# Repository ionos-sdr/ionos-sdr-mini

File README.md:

# Ionos SDR mini

Simplified, low-cost sibling of [Ionos SDR](https://github.com/ionos-sdr/ionos-sdr): a carrier PCB that turns a stock Silicon Labs radio board into a usable SDR. An ESP32-S3 DevKitC sits on female headers on the left, a Silicon Labs radio board plugs into the mezzanine socket on the right, and both displays are optional. No custom RF design, no exotic parts — the radio board you already have in a drawer does the RF.

*v1.1, 4 layers. KiCad 10 ray-traced render: DevKitC on headers, SSD1306 OLED with BACK/OK below it, the optional ER-TFTM024-3 TFT on a 2x20 socket in the middle (manufacturer's 3D model), cursor keys and the radio board connectors on the right. The render shows the shrouded Samtec TFC model; the JLC build uses the unshrouded TFM-120-02-L-D-K-TR on the same footprint.*

**Status: v1.1 (4-layer) designed, not built yet.** The built and measured board is rev-B3 2L (tag [`rev-b3-2l`](https://github.com/ionos-sdr/ionos-sdr-mini/tree/rev-b3-2l)) — ≈ 86 hours of measurements plus over-the-air receive tests ([Measurements](#measurements)). The firmware lives in the [main repository](https://github.com/ionos-sdr/ionos-sdr); this repo holds the carrier board, its documentation and its measurements.

## What it is

- **Carrier only.** 168 x 80 mm, 4-layer (JLC04161H-7628: F.Cu parts + GND / In1 solid GND / In2 power + signals, horizontal / B.Cu signals, vertical + GND), four M3 nylon standoffs. No RF layout risk: matching network, SMA and shielding stay on the Silicon Labs radio board. Earlier revisions: rev-B3 2L (built and measured, tag `rev-b3-2l`) and rev-B3 4L (branch `layout/rev-b3`).
- **Any radio board fits.** The mezzanine pair is the standard WSTK radio board interface, so BRD4265B (FG23, 434 MHz, 10 dBm) is only the first panel. The pin-to-signal mapping differs per panel and is selected in firmware.
- **Panel auto-detect.** The radio board's M24C02 board-ID EEPROM sits on the same I2C bus as the OLED, so the firmware can read which panel is plugged in and load the matching pin map at boot.
- **Bootstrap flashing.** SWDIO, SWCLK, SWO and RESET are routed to the ESP32, which bit-bangs SWD. A blank radio board can be programmed with nothing but this board and a USB cable; routine updates then go over the UART command link. For a J-Link or Simplicity Link there is also a 1x6 2.54 mm SWD footprint (CON3) on the right edge.
- **One cable.** Power and data over the DevKit's USB-C. The radio gets its own low-noise LDO from the 5 V rail, not the DevKit's shared 3.3 V.

## Architecture

- **RX**: FG23 I/Q capture and server-side FFT lines over SPI2 (IO_MUX) to the ESP32-S3, then to the host or to the on-board display.
- **Control**: RDY handshake and a UART command link; SWD is bit-banged by the ESP32 so a blank panel can be programmed with nothing but this board.
- **Power**: a single low-noise LDO feeds VMCU_IN; the radio board's own DC-DC handles PAVDD, so one supply pin powers the whole panel.

## Hardware

| Block | Part | Notes |
| --- | --- | --- |
| MCU | ESP32-S3-DevKitC-1 or the AliExpress clone | On 1x22 female headers (JLC-fitted), antenna end overhanging the board edge; see [DevKit: clone or official](#devkit-clone-or-official) |
| Radio | Silicon Labs radio board | 2x 2x20, 1.27 mm mezzanine, 24 mm apart; BRD4265B validated first |
| Display (optional) | EastRising ER-TFTM024-3, 2.4", ILI9341 | 240x320, TE pin wired for tear-free hardware scroll; resistive or capacitive touch |
| Display (optional) | SSD1306 0.96" OLED, I2C | Status line when the large display is not fitted |
| Buttons | 6+1 tactile, C&K PTS647 | UP/DOWN/LEFT/RIGHT plus BACK/OK, a seventh SPARE footprint (key optional); two resistor ladders |
| Debug (optional) | 1x6 2.54 mm SWD footprint, CON3 | Not fitted; pogo clip or solder-in pins, see below |
| Radio supply | LP5907-3.3 or TPS7A2033 | ~6.5 uVrms, fed from the DevKit 5 V rail, ferrite + 10 uF at the connector |

Seven keys cost two pins, not seven: both ladders use the same 10 k pull-up and the same 0 R / 2.2 k / 6.8 k / 22 k set to GND (UP/DOWN/LEFT/RIGHT on GPIO2, BACK/OK/SPARE on GPIO1, the 22 k level of that ladder left free), read on ADC1 with a 1 k + 100 nF filter at the pin. One threshold table serves both: 0.30 / 0.97 / 1.80 / 2.79 V. Only the 0 R keys (UP, BACK) can wake the chip from deep sleep. The freed GPIOs carry the SWD lines.

## Pin mapping (BRD4265B)

The EXP header numbers come from the Silicon Labs radio board documentation; the connector pins are what you actually route. For EXP 3 to 16 the P201 pin number equals the EXP number.

| Signal | ESP32-S3 GPIO | FG23 pin | WSTK net | Connector pin |
| --- | --- | --- | --- | --- |
| SCLK | 12 (SPI2 IO_MUX) | PC05 | WSTK_P12 | P201-15 |
| MOSI | 11 (SPI2 IO_MUX) | PC00 | WSTK_P7 | P201-10 |
| CS | 10 (SPI2 IO_MUX) | PA07 | WSTK_P10 | P201-13 |
| RDY | 14 | PD02 | WSTK_P6 | P201-9 |
| CMD | 13 (UART TX) | PA06 | WSTK_P8 | P201-11 |
| SWDIO | 38 | PA02 | WSTK_P18 | P201-21 |
| SWCLK | 39 | PA01 | WSTK_P20 | P201-23 |
| SWO | 47 | PA03 | WSTK_P16 | P201-19 |
| RESETn | 40 | RESETn | WSTK_F4 | P200-17 |
| BOARD_ID_SDA / SCL | 41 / 42 (I2C0) | - | BOARD_ID | P200-40 / P200-39 |
| VMCU_IN | - | - | VMCU_IN | P201-2 |
| 3V3 | - | - | 3V3 | P200-1 |
| GND | - | - | GND | P200-2, 38; P201-1, 39 |

The FG23 link runs on SPI2 through the IO_MUX pins so the slave interface keeps its headroom for higher clocks; the optional TFT is on SPI3. `VRF` is unused on BRD4265B and the on-board DC-DC feeds PAVDD, so a single supply pin powers the whole panel; P201-40 (VRF_IN) only runs to test point TP8, and P200-37 (5 V) has a not-fitted 0 R (R33) from the DevKit 5 V for panels that need it.

## Display and touch

The ER-TFTM024-3 sits on SPI3 (SCK 4, MOSI 5, MISO 6, CS 7, D/C 15, RST 16, BL 17, TE 18). Its resistive touch controller (XPT2046) and the module's optional SD/font/flash chips share a second header bus (pins 32/33/34), which is tied to the TFT bus on the carrier; the touch transactions run at their own ~2 MHz clock. 10 k pull-ups hold the module's SD/FONT/FLASH chip selects (header 35/36/37) inactive so nothing else drives MISO.

| Pin | Resistive (XPT2046) | Capacitive (I2C CTP) |
| --- | --- | --- |
| TCH_A, GPIO8, header 30 | SPI CS | I2C SCL |
| TCH_B, GPIO21, header 31 | PENIRQ | I2C SDA |
| TCH_INT, GPIO9, header 39 | unused | CTP INT |

Both 4.7 k pull-ups (TCH_A, TCH_B) are fitted in every build, so one BOM serves both panel types; firmware picks the mode. **Before the first power-up**, measure the panel's MISO/TE high level with VDD = 5 V: if it follows 5 V, run the panel from 3V3 or add level shifting.

## DevKit: clone or official

The two boards do not share the same header spacing. On the Espressif ESP32-S3-DevKitC-1 the two pin rows are 22.86 mm apart. The AliExpress clone is wider: its PCB is 28.3 mm, and its rows are 25.4 mm apart.

Since v1.1 the footprint has both right-hand rows:
- J1 (left) is shared.
- J3 has two rows of holes, 2.54 mm apart, joined by copper.
- The silkscreen shows both outlines (the clone's dashed) and marks the two spacings, "DevKitC-1 22.86" and "clone 25.40", under the module.

JLC fits the female headers:

| Header | Row | Fitted |
| --- | --- | --- |
| J10 | J1 (shared) | always |
| J11 | clone J3 | default |
| J12 | DevKitC-1 J3 | not fitted (DNP); fit it instead of J11 for an Espressif board |

The RGB LED is on GPIO48 on the clone and on DevKitC-1 v1.0, and on GPIO38 on DevKitC-1 v1.1. The SWD lines avoid GPIO48: since v1.1 SWO is on **GPIO47**, SWDIO stays on GPIO38. With a DevKitC-1 v1.1 the LED sits on SWDIO, flickers during SWD and loads the line, so remove the LED or its series resistor, or use the clone or a v1.0 board.

## Changes in v1.1

- DevKit footprint with two J3 rows (clone 25.4 mm and DevKitC-1 22.86 mm), J10-J12 female headers in the JLC BOM (Hong Cheng HC-PM254-8.5H-1x22PZ, THT).
- SWO moved from GPIO48 to GPIO47 (GPIO48 drives the clone's RGB LED).
- OLED: four 2.5 mm plated holes for the module's mounting lugs, and the outline per the module drawing (27.3 x 27.3 mm).
- TFT socket is SMD (HCTL PM254-2-20-S-8.5, 8.5 mm), assembled by JLC.
- Layer roles: In1 is solid GND, as the reference for the top layer. In2 carries the power and most signals, routed horizontally (89 % of its length); B.Cu takes the vertical runs (79 %). The top layer holds only the parts' escapes (153 mm). The board was fully re-routed and GND-stitched.

## SWD debug header

CON3 is a 1x6 2.54 mm row of plated holes on the right edge, outside the radio board's outline, so it stays reachable with the radio board plugged in. Pin order follows the Tag-Connect TC2030-CTX:

| Pin | 1 | 2 | 3 | 4 | 5 | 6 |
| --- | --- | --- | --- | --- | --- | --- |
| Signal | VTref (VMCU) | SWDIO | nRESET | SWCLK | GND | SWO |

The pins connect on the radio side of the solder-jumper cut points. With a debugger attached, either keep the ESP32's SWD pins as inputs in firmware or cut JP2 and JP6-JP8 to detach the ESP32 completely. VTref only senses the radio board's VMCU; the debugger must not power the board through it.

## Measurements

All measurements so far are on **rev-B3 2L** + BRD4265B, the board that was built (tag [`rev-b3-2l`](https://github.com/ionos-sdr/ionos-sdr-mini/tree/rev-b3-2l)); v1.1 has not been built yet.

**Time on test so far: ≈ 86 hours** (rev-B3 2L + BRD4265B, 2–9 Nov 2026): ≈ 54 h RF with a calibrated signal generator, ≈ 32 h USB-only soaks.
Full report: [`docs/ionos-mini-measurements-2026-11.md`](docs/ionos-mini-measurements-2026-11.md) ([magyarul](docs/hu/ionos-mini-meresi-jelentes-2026-11.md)) · raw data and scripts: [`measurements/ionos-mini-2026-11/`](measurements/ionos-mini-2026-11/).

| BRD4265B (434 MHz match), measured at 145 MHz | |
|---|---|
| I/Q over USB (TinyUSB CDC on USB‑OTG) | 200 ksps int16 (813 kB/s); 40 h: 86 M blocks, 0 device drops, 0.65 ppm host loss |
| Gain / clipping | dBFS = P_in + 53.68 dB (σ 0.10 dB over 40 h), clip ≈ −52 dBm |
| NF / MDS | ≈ 8.6 dB / ≈ −128 dBm (10 dB SNR, 500 Hz) |
| 200 ksps bandwidth / image rejection | 88 kHz at −3 dB (PHY channel filter) / ≥ 42 dB |
| Frequency | crystal +4.2 ppm raw (firmware correction currently over-corrects to −11 ppm), 1.9 ppm p‑p diurnal |
| Tuning range with the 145 MHz PHY | 128.34 – 198.07 MHz; CW NF 7.9 – 11.9 dB across it |
| 2‑FSK 5 kbps, BER 10⁻² | median −110 dBm (simple discriminator reference) |
| SoapySDR | SoapyIonos driver works on Windows (GQRX, SoapySDRUtil, Python); 3.25 M blocks in the sweeps, 4 lost |
| Known artefact | ±6.25 kHz sidebands (−74 dBc at 5 kHz, −43 dBc at 37 kHz tone offset) from the I/Q path — open |

### Receive tests, 22 Nov 2026 — APRS, AIS, ground loop

Over the air at home (Budapest, ~1 km from the Danube), mag‑mount 2 m whip on a radiator. Details: [`measurements/ionos-mini-2026-11-22-rx/`](measurements/ionos-mini-2026-11-22-rx/RESULT.md).

| | |
|---|---|
| APRS 144.800, on‑device AFSK demod | channel FIR before the discriminator: 20 of 20 bursts on a 20‑min capture (old firmware 0); ~25 packets/h gated live |
| AIS 161.975 (channel A), on‑device GMSK demod | battery supply: 56 of 63 bursts (89 %); live 70 min: 788 messages, 82 stations (64 river AtoN, 14 vessels); NMEA on TCP 10110 |
| AIS per‑packet level / SNR / offset | −46 … −36 dBFS, SNR 9–25 dB (median 15), ±600 Hz |
| **Ground loop** (mains‑charged laptop USB + antenna on a radiator, no PE in the house) | 12–17 dB gain dips, 2–4 ms, every 20 ms: AIS 13 of 398 bursts, APRS dead after dark. **Use a battery or isolate the USB.** |

<p align="center"><i>On‑device TFT waterfall (PC emulator of the firmware): old vs new — per‑bin peak of the 3 FFTs per row, 24 dB range, DC patch ±1 bin.</i></p>

### AIS: I/Q path vs FG23 on-chip, 23 Nov 2026 — VSG60 and live

Same firmware, two receive modes: the ESP32 demodulates the FG23's I/Q stream, or the FG23 decodes AIS itself (own PHY, LEGACY demod, HDLC/CRC on-chip). Details: [`measurements/ionos-mini-2026-11-23-ais-onchip/`](measurements/ionos-mini-2026-11-23-ais-onchip/RESULT.md).

| | I/Q path | FG23 on-chip |
|---|---|---|
| 50 % PER (VSG, 10 bursts/s, 26 cycles overnight) | −106.19 dBm (sd 0.17) | −105.45 dBm (sd 0.10) |
| frequency offset at −103 dBm, PER ≤ 7 % | about ±1 kHz | about ±3 kHz |
| CW on channel B (+50 kHz), +30 dBc | channel A blocked (alias) | no loss up to +50 dBc |
| every slot busy (37.5 bursts/s, −96 dBm) | 0 % | 0 % |
| live, 15 h alternating (Danube) | 1.67 msgs/min (721) | 2.08 msgs/min (902) |
| channels | A | A or B |

**Full AIS report (PDF, rev. 2, 26 Nov 2026)** - instrument (VSG60A) and field tests, test hours, charts, and **dual-channel I/Q: channels A and B at the same time from one FG23, measured overnight** (no sensitivity cost, +/-4 kHz offset tolerance with AFC): [English](docs/reports/ionos-mini_AIS_report_EN_2026-11-26.pdf)  [Magyar](docs/reports/ionos-mini_AIS_jelentes_HU_2026-11-26.pdf). Dual-channel data: [`measurements/ionos-mini-2026-11-25-ais-dual/`](measurements/ionos-mini-2026-11-25-ais-dual/RESULT.md). First edition (25 Nov): [EN](docs/reports/ionos-mini_AIS_report_EN_2026-11-25.pdf) [HU](docs/reports/ionos-mini_AIS_jelentes_HU_2026-11-25.pdf). Live AISBENCH log and the chart/report scripts are in [`measurements/ionos-mini-2026-11-23-ais-onchip/`](measurements/ionos-mini-2026-11-23-ais-onchip/).

## Manufacturing files

Gerbers, drill, JLCPCB BOM and CPL are attached to the GitHub release [`rev-b3-4l-20261022`](https://github.com/ionos-sdr/ionos-sdr-mini/releases/tag/rev-b3-4l-20261022), not committed. To rebuild them from the KiCad project (DRC and schematic parity must be clean, or nothing is written):

```
"C:\Program Files\KiCad\10.0\bin\python.exe" fab/jlc_pack.py
```

JLC assembles the top-side SMD parts, the two radio board connectors, the TFT socket and the DevKit headers (J10 + J11 for the clone by default); the DevKit, the displays and the debug header are fitted by hand. The manufacturing files for v1.1 have not been released yet; the release above is rev-B3 4L, and the built 2L board's files are in [`rev-b3-2l-jlc-20261022`](https://github.com/ionos-sdr/ionos-sdr-mini/releases/tag/rev-b3-2l-jlc-20261022). LCSC part numbers are in `fab/jlc_lcsc.csv`.

## Repository

```
hardware/          KiCad project, fab outputs, BOM           CERN-OHL-P-2.0
docs/              pin mapping, assembly notes, renders      CC-BY-4.0
measurements/      raw data, scripts, results                CC-BY-4.0
firmware/          ESP32-S3 + FG23 source snapshot           MIT
```

Firmware is developed in the [main repository](https://github.com/ionos-sdr/ionos-sdr) (`firmware-fg23/`, `firmware-esp32/`); [`firmware/`](firmware/) here is the snapshot that runs on the measured units, with both AIS receive modes (I/Q and FG23 on-chip). See [`firmware/README.md`](firmware/README.md).

## Credits, licensing, trademarks

Hardware under CERN-OHL-P-2.0, documentation under CC-BY-4.0. Not affiliated with IONOS SE or Silicon Laboratories; EFR32, Simplicity Studio and the WSTK radio board interface are Silicon Labs property, used here for interoperability only.

Designed by Zoltán Dóczi and Zoltán Papp at [Z2 Labs](https://www.z2labs.io/), Budapest. Design and manufacturing support by [Protowoerk](https://www.protowoerk.com).

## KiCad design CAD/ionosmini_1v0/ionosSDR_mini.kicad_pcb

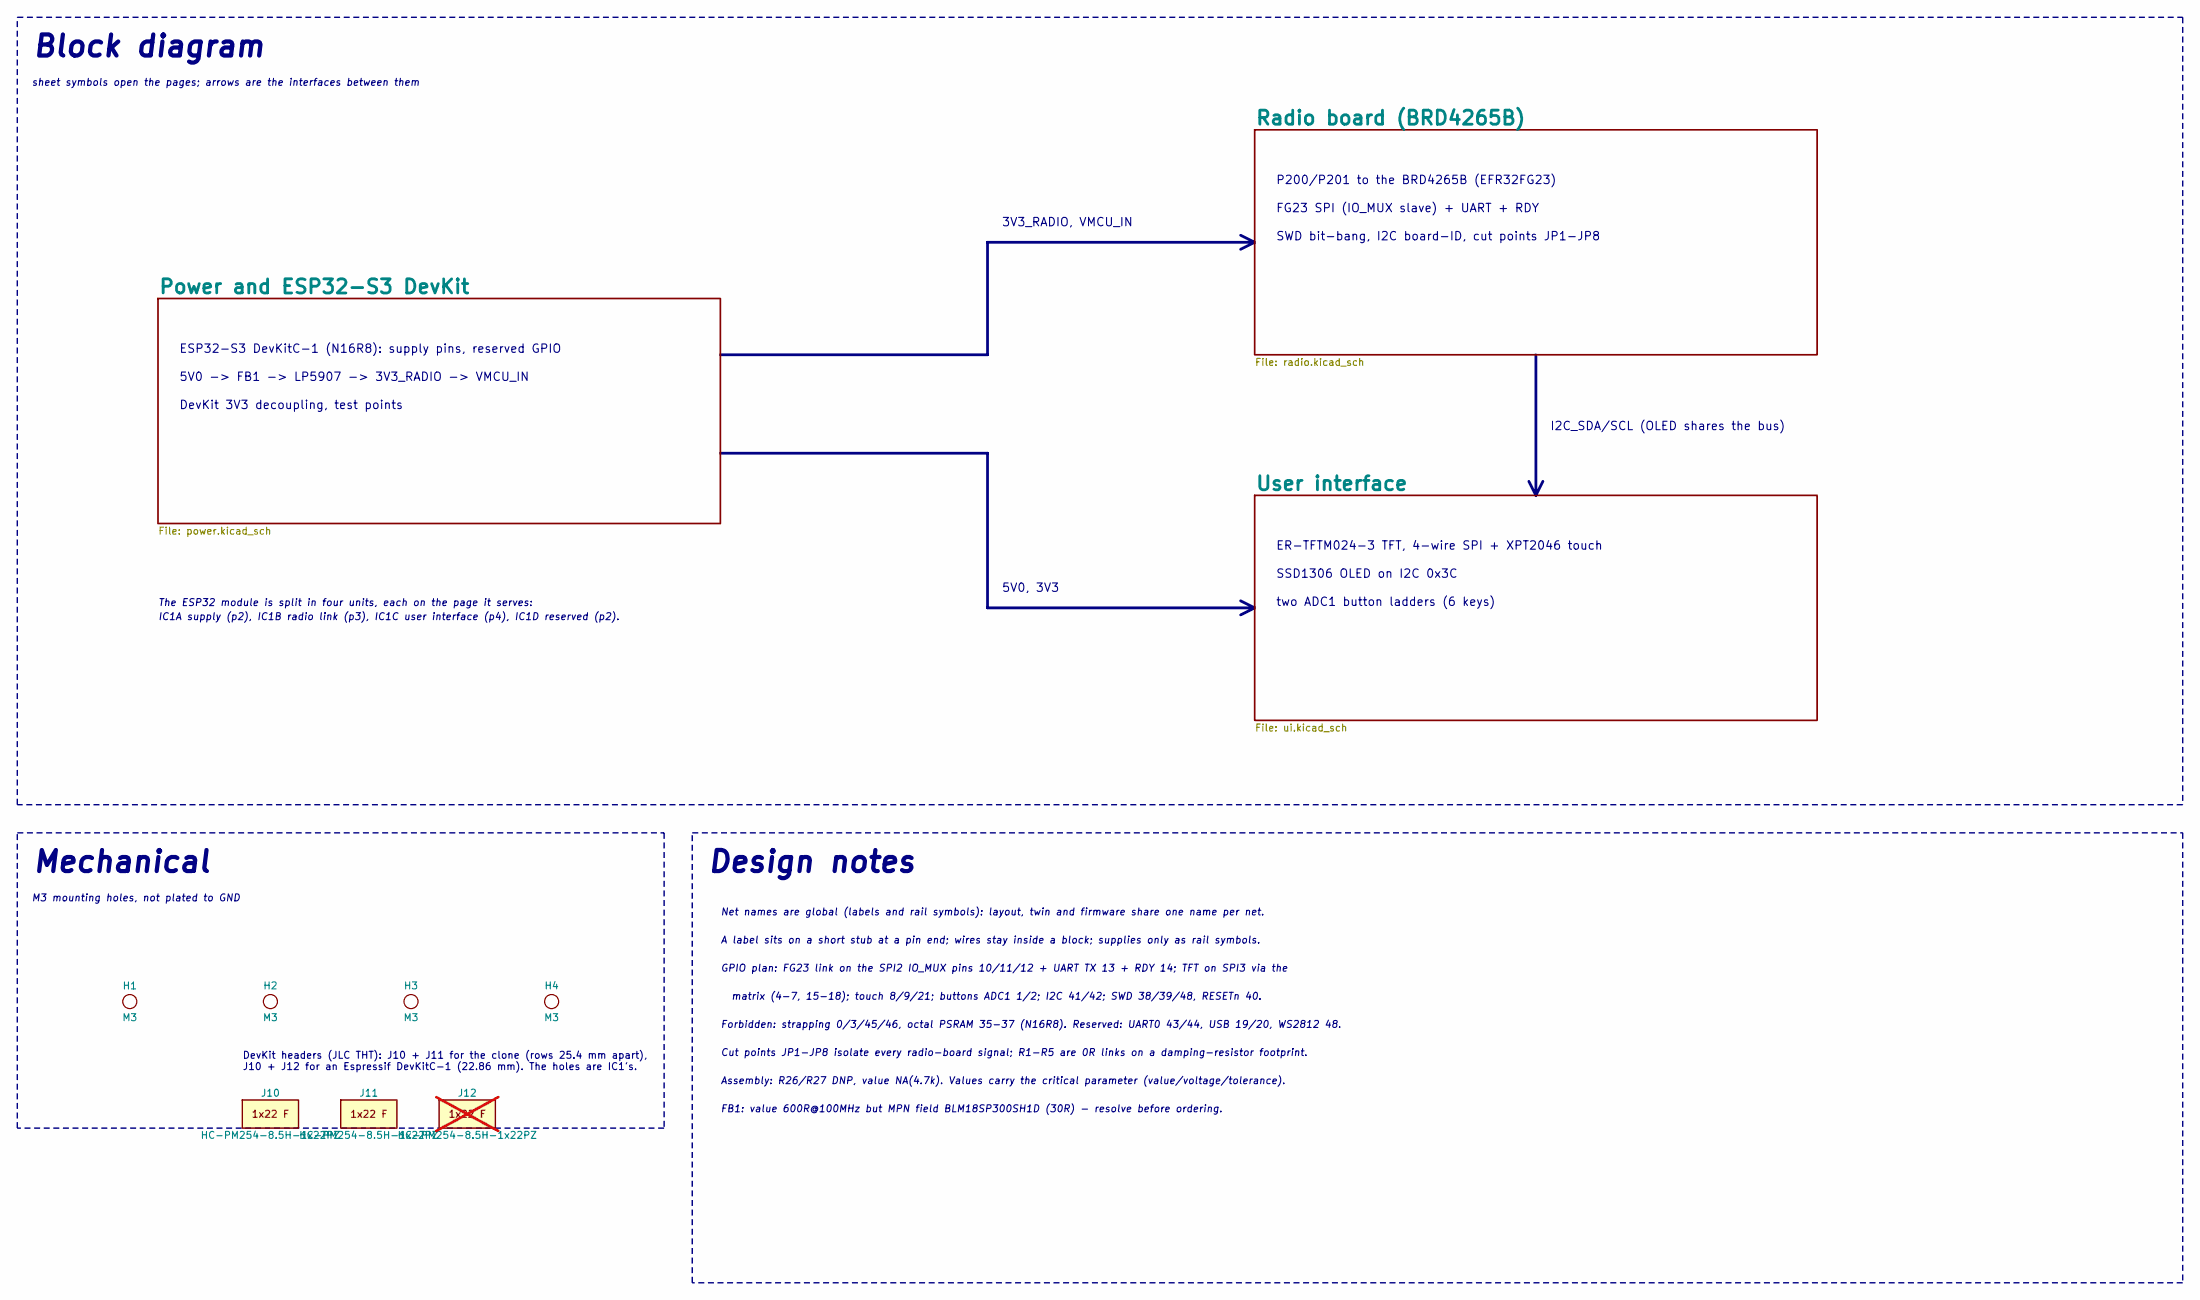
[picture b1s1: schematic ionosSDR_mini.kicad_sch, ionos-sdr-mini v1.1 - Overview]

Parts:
H1, H2, H3, H4: M3; PB_HOLE
J10, J11: HC-PM254-8.5H-1x22PZ; DevKit_Socket_1x22_THT
J12: HC-PM254-8.5H-1x22PZ; DevKit_Socket_1x22_THT; not fitted

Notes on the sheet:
Block diagram
sheet symbols open the pages; arrows are the interfaces between them
ESP32-S3 DevKitC-1 (N16R8): supply pins, reserved GPIO
5V0 -> FB1 -> LP5907 -> 3V3_RADIO -> VMCU_IN
DevKit 3V3 decoupling, test points
P200/P201 to the BRD4265B (EFR32FG23)
FG23 SPI (IO_MUX slave) + UART + RDY
SWD bit-bang, I2C board-ID, cut points JP1-JP8
ER-TFTM024-3 TFT, 4-wire SPI + XPT2046 touch
SSD1306 OLED on I2C 0x3C
two ADC1 button ladders (6 keys)
3V3_RADIO, VMCU_IN
5V0, 3V3
I2C_SDA/SCL (OLED shares the bus)
The ESP32 module is split in four units, each on the page it serves:
IC1A supply (p2), IC1B radio link (p3), IC1C user interface (p4), IC1D reserved (p2).
Mechanical
M3 mounting holes, not plated to GND
Design notes
Net names are global (labels and rail symbols): layout, twin and firmware share one name per net.
A label sits on a short stub at a pin end; wires stay inside a block; supplies only as rail symbols.
GPIO plan: FG23 link on the SPI2 IO_MUX pins 10/11/12 + UART TX 13 + RDY 14; TFT on SPI3 via the
matrix (4-7, 15-18); touch 8/9/21; buttons ADC1 1/2; I2C 41/42; SWD 38/39/48, RESETn 40.
Forbidden: strapping 0/3/45/46, octal PSRAM 35-37 (N16R8). Reserved: UART0 43/44, USB 19/20, WS2812 48.
Cut points JP1-JP8 isolate every radio-board signal; R1-R5 are 0R links on a damping-resistor footprint.
Assembly: R26/R27 DNP, value NA(4.7k). Values carry the critical parameter (value/voltage/tolerance).
FB1: value 600R@100MHz but MPN field BLM18SP300SH1D (30R) - resolve before ordering.
DevKit headers (JLC THT): J10 + J11 for the clone (rows 25.4 mm apart), J10 + J12 for an Espressif DevKitC-1 (22.86 mm). The holes are IC1's.

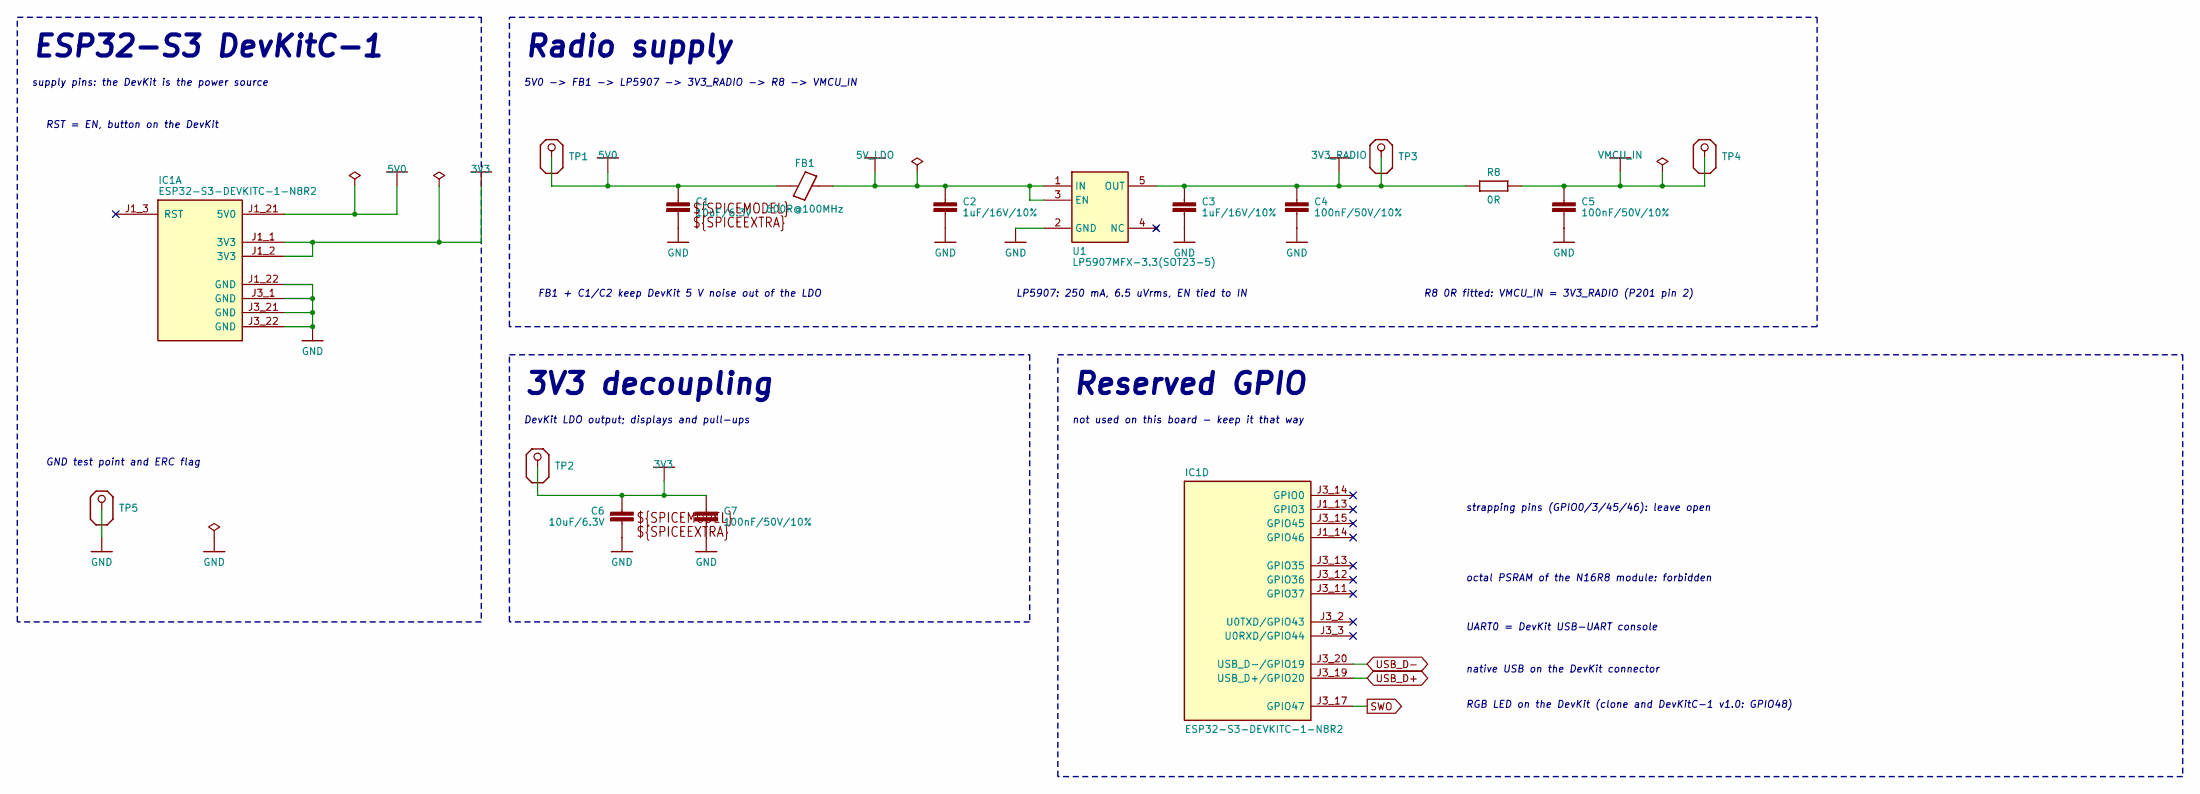
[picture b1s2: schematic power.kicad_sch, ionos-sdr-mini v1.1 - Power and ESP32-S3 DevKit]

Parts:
C1, C6: 10uF/6.3V; CAPC1005X60_0402
C2, C3: 1uF/16V/10%; CAPC1005X60_0402; MPN CL05A105KO5NNNC
C4, C5, C7: 100nF/50V/10%; CAPC1005X60_0402; MPN GRM155R71H104KE14D
FB1: 600R@100MHz; L5_0603; MPN BLM18SP300SH1D
IC1: ESP32-S3-DEVKITC-1-N8R2; XCVR_ESP32-S3-DEVKITC-1-N8R2; MPN ESP32-S3-DEVKITC-1-N8R2
R8: 0R; RESC1005X40_0402; MPN CRCW04020000Z0EDC
TP1: 5V0; TESTPOINT_40MIL_SMD
TP2: 3V3; TESTPOINT_40MIL_SMD
TP3: 3V3_RADIO; TESTPOINT_40MIL_SMD
TP4: VMCU_IN; TESTPOINT_40MIL_SMD
TP5: GND; TESTPOINT_40MIL_SMD
U1: LP5907MFX-3.3(SOT23-5); SOT-23-5; MPN LP5907MFX-3.3/NOPB

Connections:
3V3: C6.1, C7.1, IC1.J1_1 (3V3), IC1.J1_2 (3V3), TP2.PP; also elsewhere on the board
3V3_RADIO: C3.1, C4.1, R8.1, TP3.PP, U1.5 (OUT); also elsewhere on the board
5V0: C1.1, FB1.1, IC1.J1_21 (5V0), TP1.PP; also elsewhere on the board
5V_LDO: C2.1, FB1.2, U1.1 (IN), U1.3 (EN)
GND: C1.2, C2.2, C3.2, C4.2, C5.2, C6.2, C7.2, IC1.J1_22 (GND), IC1.J3_1 (GND), IC1.J3_21 (GND), IC1.J3_22 (GND), TP5.PP, U1.2 (GND); also elsewhere on the board
SWO: IC1.J3_17 (GPIO47); also elsewhere on the board
USB_D+: IC1.J3_19 (USB_D+/GPIO20)
USB_D-: IC1.J3_20 (USB_D-/GPIO19)
VMCU_IN: C5.1, R8.2, TP4.PP; also elsewhere on the board

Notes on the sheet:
ESP32-S3 DevKitC-1
supply pins: the DevKit is the power source
GND test point and ERC flag
RST = EN, button on the DevKit
Radio supply
5V0 -> FB1 -> LP5907 -> 3V3_RADIO -> R8 -> VMCU_IN
FB1 + C1/C2 keep DevKit 5 V noise out of the LDO
LP5907: 250 mA, 6.5 uVrms, EN tied to IN
R8 0R fitted: VMCU_IN = 3V3_RADIO (P201 pin 2)
3V3 decoupling
DevKit LDO output; displays and pull-ups
Reserved GPIO
not used on this board - keep it that way
strapping pins (GPIO0/3/45/46): leave open
octal PSRAM of the N16R8 module: forbidden
UART0 = DevKit USB-UART console
native USB on the DevKit connector
RGB LED on the DevKit (clone and DevKitC-1 v1.0: GPIO48)

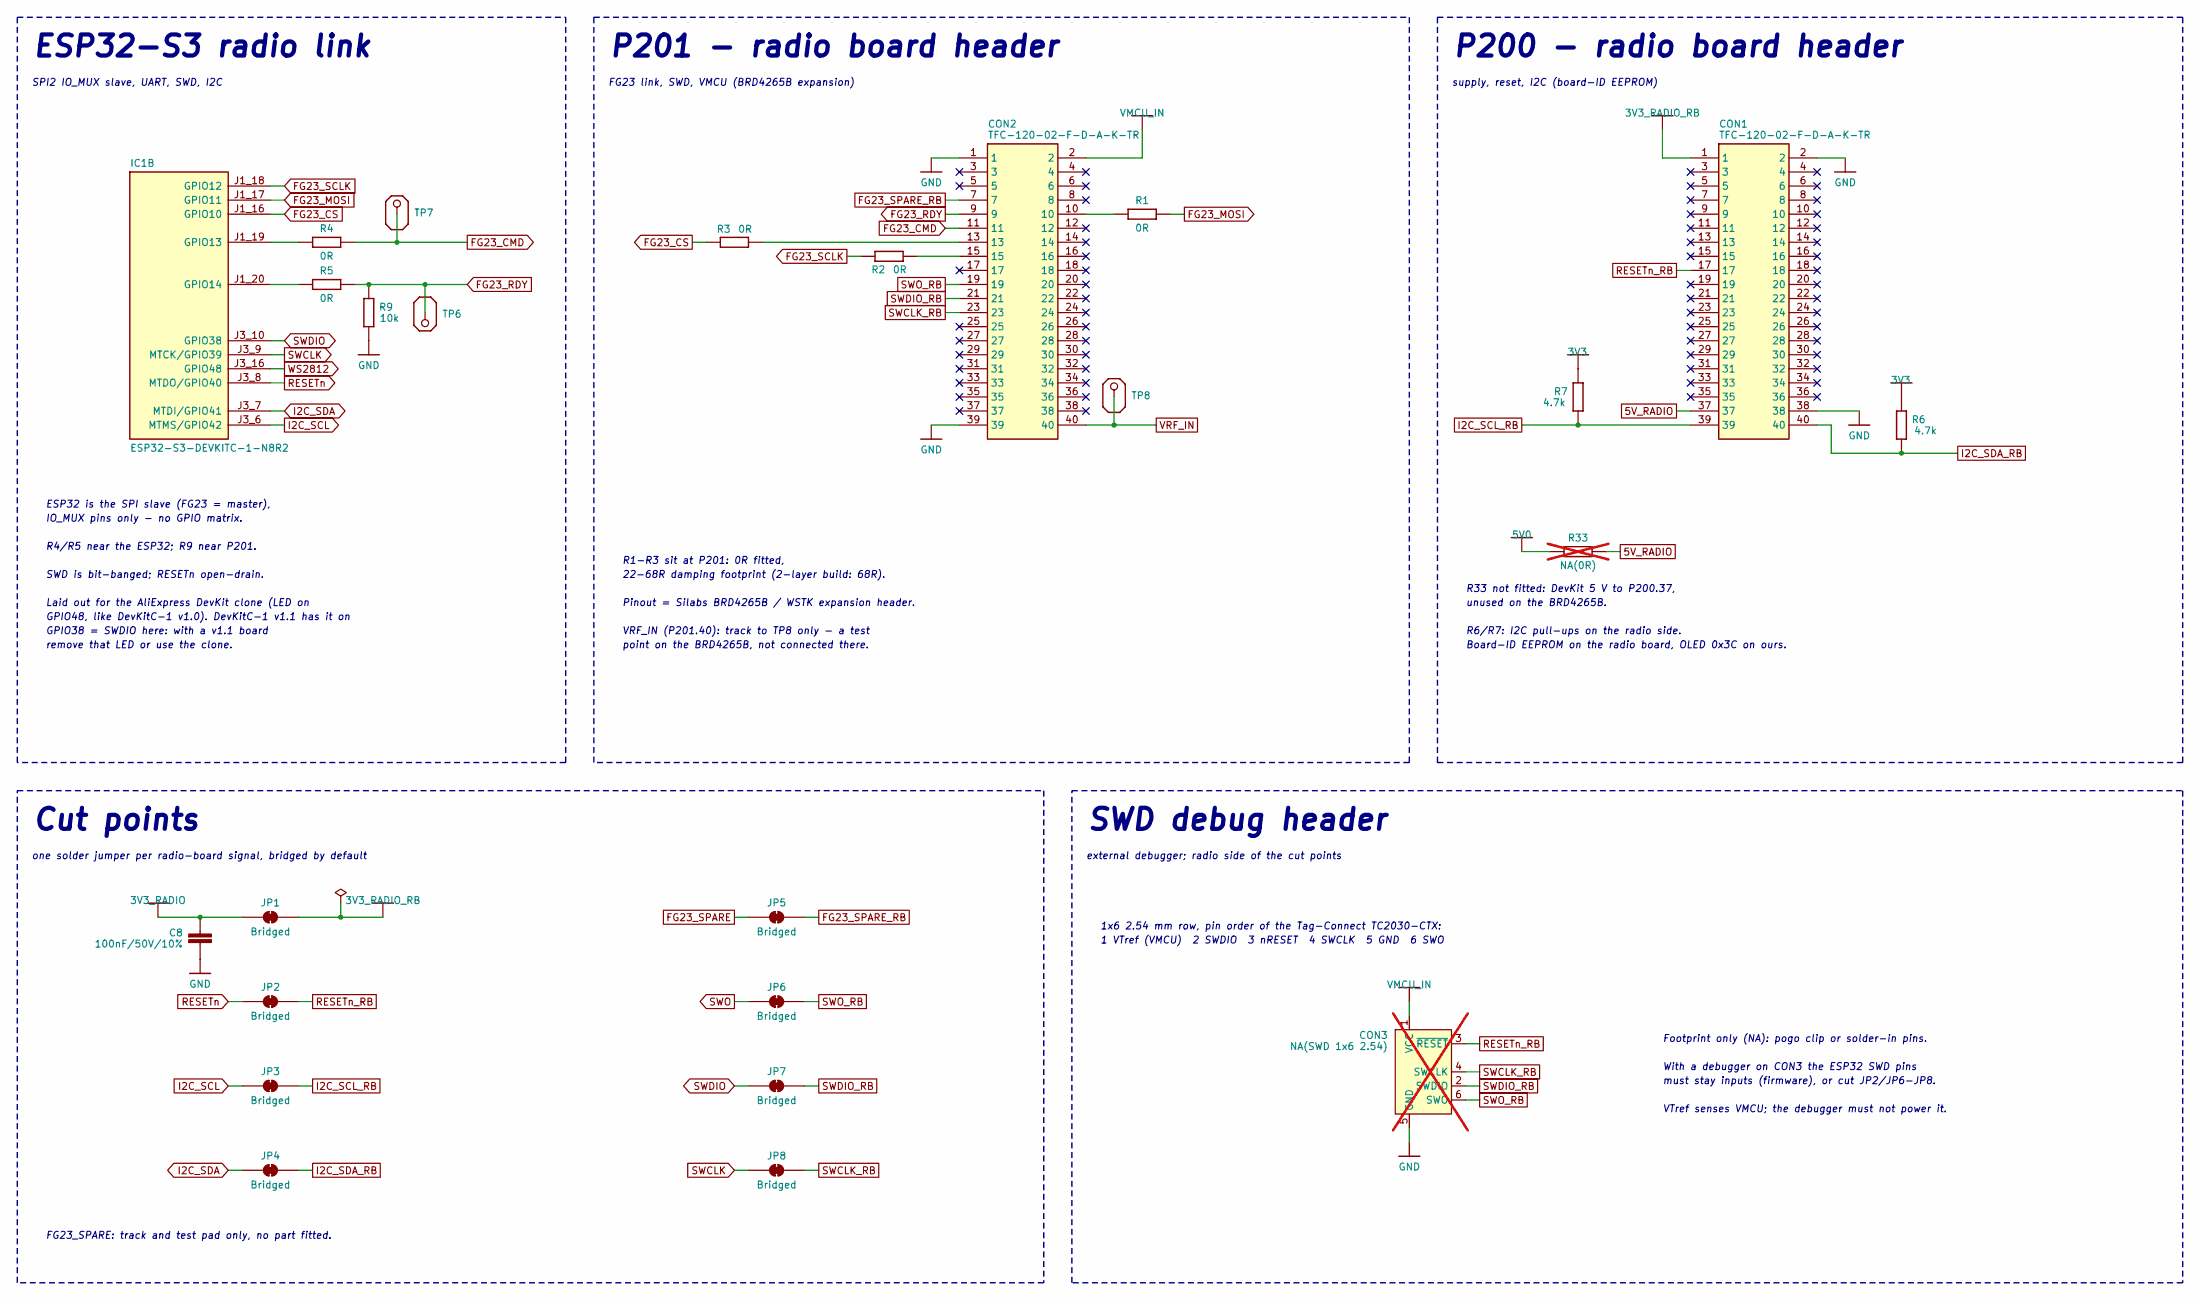
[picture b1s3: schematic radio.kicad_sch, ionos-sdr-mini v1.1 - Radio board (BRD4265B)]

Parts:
C8: 100nF/50V/10%; CAPC1005X60_0402; MPN GRM155R71H104KE14D
CON1, CON2: TFC-120-02-F-D-A-K-TR; TFC-120-02-XX-D-A-K-TR; MPN TFC-120-02-F-D-A-K-TR
CON3: NA(SWD 1x6 2.54); PinHeader_1x06_P2.54mm_Vertical; not fitted
IC1: ESP32-S3-DEVKITC-1-N8R2; XCVR_ESP32-S3-DEVKITC-1-N8R2; MPN ESP32-S3-DEVKITC-1-N8R2
JP1, JP2, JP3, JP4, JP5, JP6, JP7, JP8: Bridged; SolderJumper-2_P1.3mm_Bridged_RoundedPad1.0x1.5mm
R1, R2, R3, R4, R5: 0R; RESC1005X40_0402; MPN CRCW04020000Z0EDC
R6, R7: 4.7k; RESC1005X40_0402; MPN CR0402AJW-472GAS
R9: 10k; RESC1005X40_0402; MPN CRCW040210K0FKED
R33: NA(0R); RESC1005X40_0402; MPN CRCW04020000Z0EDC; not fitted
TP6: FG23_RDY; TESTPOINT_40MIL_SMD
TP7: FG23_CMD; TESTPOINT_40MIL_SMD
TP8: VRF_IN; TESTPOINT_40MIL_SMD

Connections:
3V3: R6.2, R7.2; also elsewhere on the board
3V3_RADIO: C8.1, JP1.1 (A); also elsewhere on the board
3V3_RADIO_RB: CON1.1, JP1.2 (B)
5V0: R33.1; also elsewhere on the board
5V_RADIO: CON1.37, R33.2
FG23_CMD: CON2.11, R4.1, TP7.PP
FG23_CS: IC1.J1_16 (GPIO10), R3.1
FG23_MOSI: IC1.J1_17 (GPIO11), R1.2
FG23_RDY: CON2.9, R5.1, R9.1, TP6.PP
FG23_SCLK: IC1.J1_18 (GPIO12), R2.1
FG23_SPARE: JP5.1 (A)
FG23_SPARE_RB: CON2.7, JP5.2 (B)
GND: C8.2, CON1.2, CON1.38, CON2.1, CON2.39, CON3.5 (GND), R9.2; also elsewhere on the board
I2C_SCL: IC1.J3_6 (MTMS/GPIO42), JP3.1 (A); also elsewhere on the board
I2C_SCL_RB: CON1.39, JP3.2 (B), R7.1
I2C_SDA: IC1.J3_7 (MTDI/GPIO41), JP4.1 (A); also elsewhere on the board
I2C_SDA_RB: CON1.40, JP4.2 (B), R6.1
unnamed: CON2.10, R1.1
unnamed: CON2.13, R3.2
unnamed: CON2.15, R2.2
unnamed: IC1.J1_19 (GPIO13), R4.2
unnamed: IC1.J1_20 (GPIO14), R5.2
RESETn: IC1.J3_8 (MTDO/GPIO40), JP2.1 (A)
RESETn_RB: CON1.17, CON3.3 (~RESET), JP2.2 (B)
SWCLK: IC1.J3_9 (MTCK/GPIO39), JP8.1 (A)
SWCLK_RB: CON2.23, CON3.4 (SWCLK), JP8.2 (B)
SWDIO: IC1.J3_10 (GPIO38), JP7.1 (A)
SWDIO_RB: CON2.21, CON3.2 (SWDIO), JP7.2 (B)
SWO: JP6.1 (A); also elsewhere on the board
SWO_RB: CON2.19, CON3.6 (SWO), JP6.2 (B)
VMCU_IN: CON2.2, CON3.1 (VCC); also elsewhere on the board
VRF_IN: CON2.40, TP8.PP
WS2812: IC1.J3_16 (GPIO48)

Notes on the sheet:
ESP32-S3 radio link
SPI2 IO_MUX slave, UART, SWD, I2C
ESP32 is the SPI slave (FG23 = master),
IO_MUX pins only - no GPIO matrix.
R4/R5 near the ESP32; R9 near P201.
SWD is bit-banged; RESETn open-drain.
Laid out for the AliExpress DevKit clone (LED on
GPIO48, like DevKitC-1 v1.0). DevKitC-1 v1.1 has it on
GPIO38 = SWDIO here: with a v1.1 board
remove that LED or use the clone.
P201 - radio board header
FG23 link, SWD, VMCU (BRD4265B expansion)
VRF_IN (P201.40): track to TP8 only - a test
point on the BRD4265B, not connected there.
R1-R3 sit at P201: 0R fitted,
22-68R damping footprint (2-layer build: 68R).
Pinout = Silabs BRD4265B / WSTK expansion header.
P200 - radio board header
supply, reset, I2C (board-ID EEPROM)
R33 not fitted: DevKit 5 V to P200.37,
unused on the BRD4265B.
R6/R7: I2C pull-ups on the radio side.
Board-ID EEPROM on the radio board, OLED 0x3C on ours.
Cut points
one solder jumper per radio-board signal, bridged by default
FG23_SPARE: track and test pad only, no part fitted.
SWD debug header
external debugger; radio side of the cut points
1x6 2.54 mm row, pin order of the Tag-Connect TC2030-CTX:
1 VTref (VMCU) 2 SWDIO 3 nRESET 4 SWCLK 5 GND 6 SWO
Footprint only (NA): pogo clip or solder-in pins.
With a debugger on CON3 the ESP32 SWD pins
must stay inputs (firmware), or cut JP2/JP6-JP8.
VTref senses VMCU; the debugger must not power it.

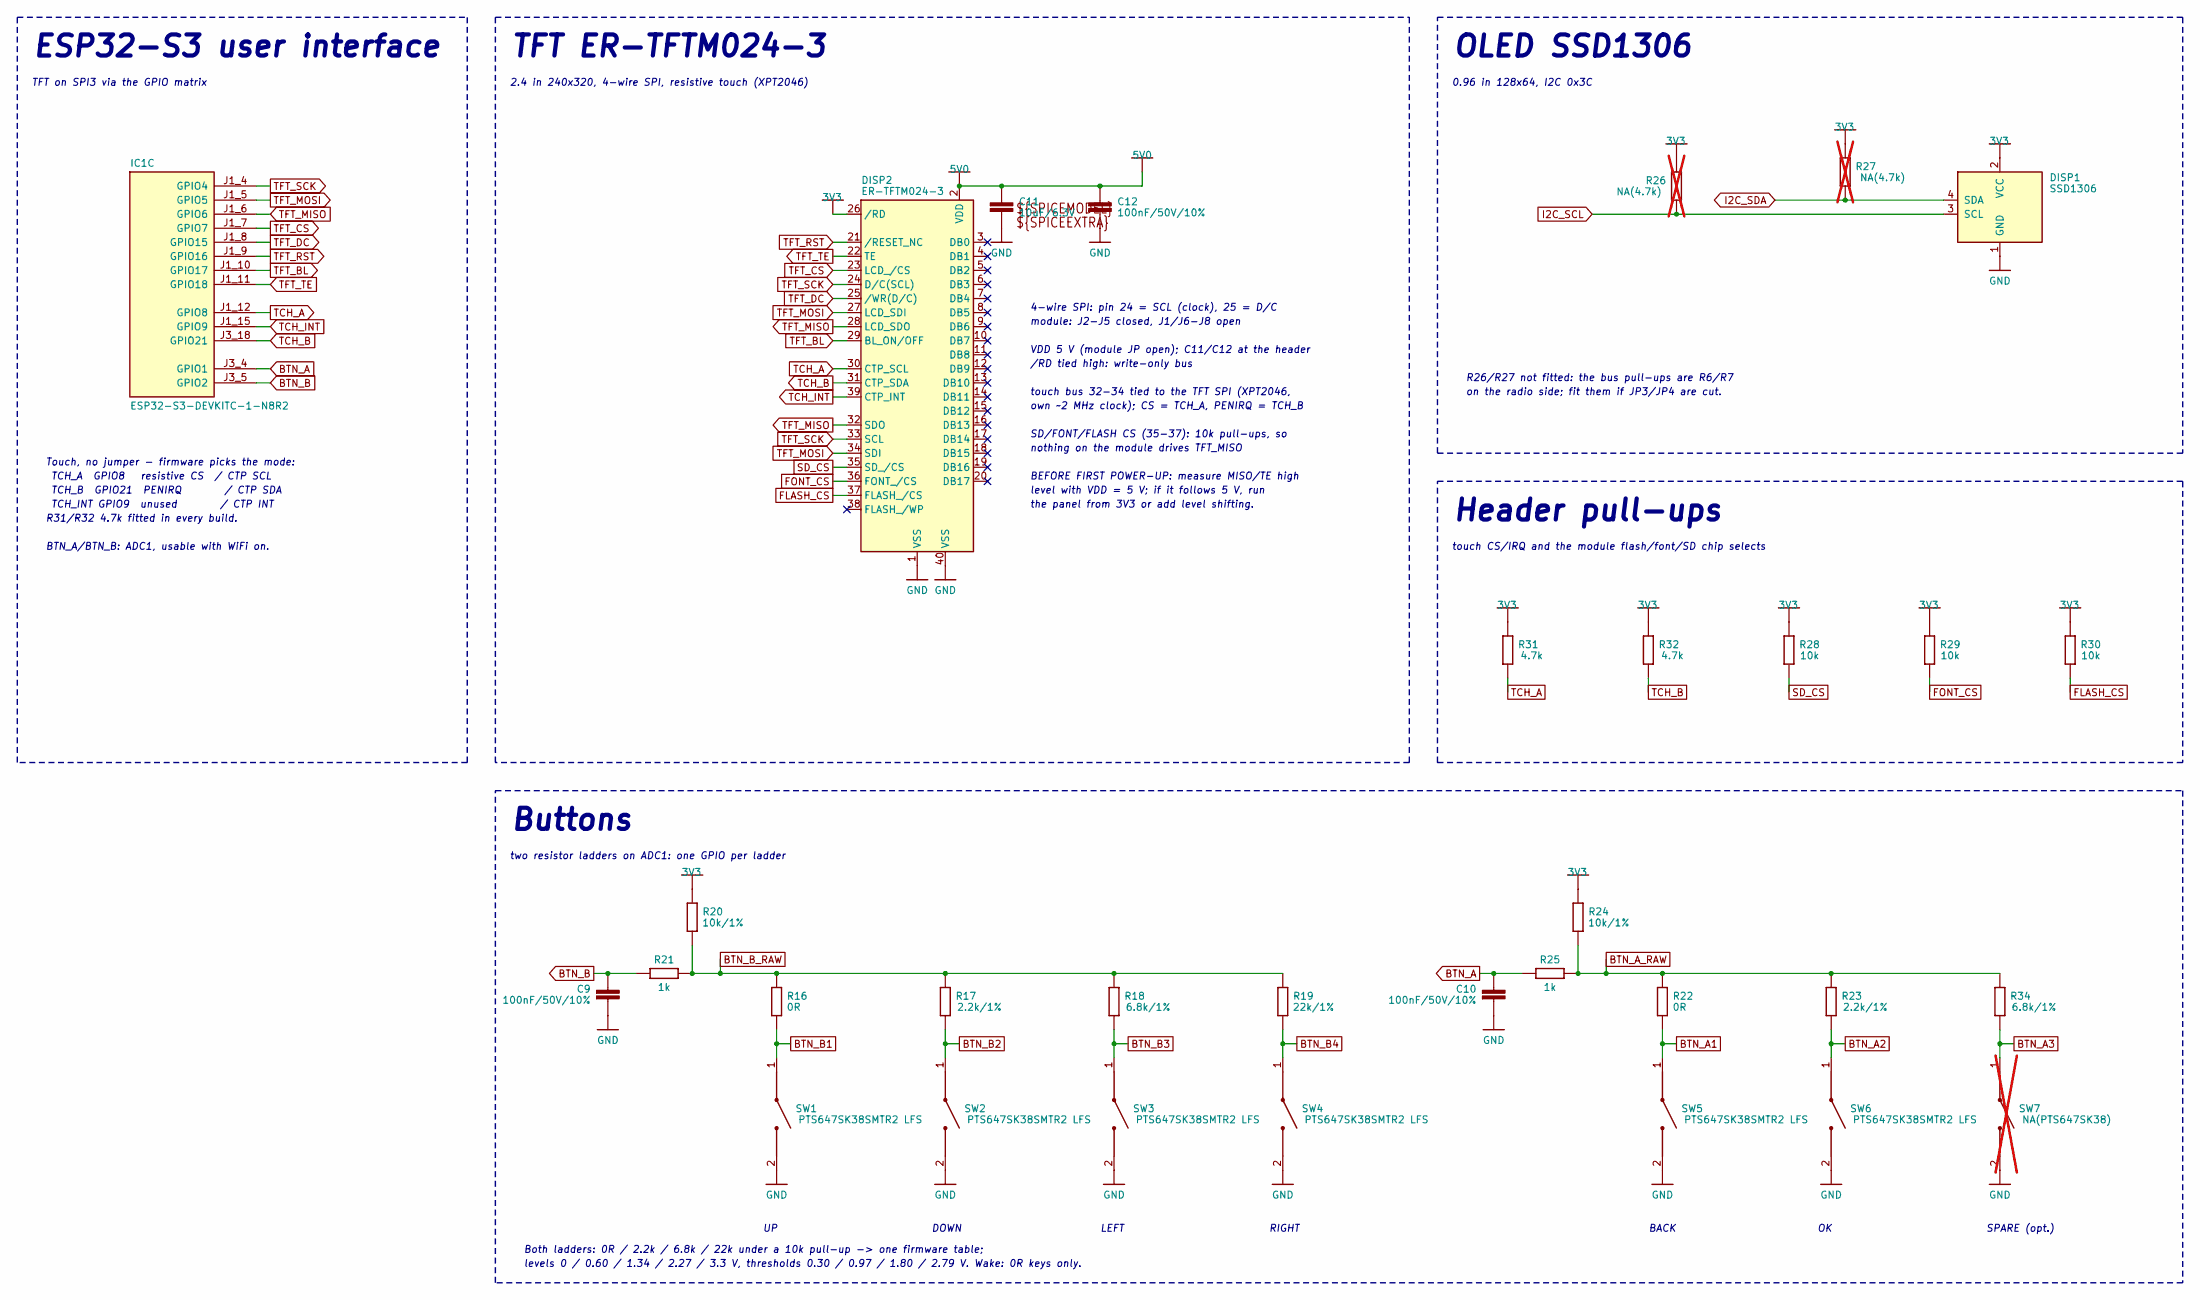
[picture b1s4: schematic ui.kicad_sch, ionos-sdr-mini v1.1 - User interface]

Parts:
C9, C10, C12: 100nF/50V/10%; CAPC1005X60_0402; MPN GRM155R71H104KE14D
C11: 10uF/6.3V; CAPC1005X60_0402
DISP1: SSD1306; 128x64OLED; MPN OLED 4pin BLUE
DISP2: ER-TFTM024-3; ER-TFTM024-3_Socket_2x20_P2.54mm
IC1: ESP32-S3-DEVKITC-1-N8R2; XCVR_ESP32-S3-DEVKITC-1-N8R2; MPN ESP32-S3-DEVKITC-1-N8R2
R16, R22: 0R; RESC1005X40_0402; MPN CRCW04020000Z0EDC
R17, R23: 2.2k/1%; RESC1005X40_0402; MPN RT0402FRE072K2L
R18, R34: 6.8k/1%; RESC1005X40_0402; MPN RC0402FR-136K8L
R19: 22k/1%; RESC1005X70_0402; MPN ERA-2AED223X
R20, R24: 10k/1%; RESC1005X40_0402; MPN CRCW040210K0FKED
R21, R25: 1k; RESC1005X40_0402; MPN CR0402-FX-1001GLF
R26, R27: NA(4.7k); RESC1005X40_0402; MPN CR0402AJW-472GAS; not fitted
R28, R29, R30: 10k; RESC1005X40_0402; MPN CRCW040210K0FKED
R31, R32: 4.7k; RESC1005X40_0402; MPN CR0402AJW-472GAS
SW1, SW2, SW3, SW4, SW5, SW6: PTS647SK38SMTR2 LFS; PTS647SK38SMTR2LFS; MPN PTS647SK38SMTR2 LFS
SW7: NA(PTS647SK38); PTS647SK38SMTR2LFS; MPN PTS647SK38SMTR2 LFS; not fitted

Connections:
3V3: DISP1.2 (VCC), DISP2.26 (/RD), R20.1, R24.1, R26.1, R27.1, R28.1, R29.1, R30.1, R31.1, R32.1; also elsewhere on the board
5V0: C11.1, C12.1, DISP2.2 (VDD); also elsewhere on the board
BTN_A: C10.1, IC1.J3_4 (GPIO1), R25.2
BTN_A1: R22.2, SW5.1
BTN_A2: R23.2, SW6.1
BTN_A3: R34.2, SW7.1
BTN_A_RAW: R22.1, R23.1, R24.2, R25.1, R34.1
BTN_B: C9.1, IC1.J3_5 (GPIO2), R21.2
BTN_B1: R16.2, SW1.1
BTN_B2: R17.2, SW2.1
BTN_B3: R18.2, SW3.1
BTN_B4: R19.2, SW4.1
BTN_B_RAW: R16.1, R17.1, R18.1, R19.1, R20.2, R21.1
FLASH_CS: DISP2.37 (FLASH_/CS), R30.2
FONT_CS: DISP2.36 (FONT_/CS), R29.2
GND: C9.2, C10.2, C11.2, C12.2, DISP1.1 (GND), DISP2.1 (VSS), DISP2.40 (VSS), SW1.2, SW2.2, SW3.2, SW4.2, SW5.2, SW6.2, SW7.2; also elsewhere on the board
I2C_SCL: DISP1.3 (SCL), R26.2; also elsewhere on the board
I2C_SDA: DISP1.4 (SDA), R27.2; also elsewhere on the board
SD_CS: DISP2.35 (SD_/CS), R28.2
TCH_A: DISP2.30 (CTP_SCL), IC1.J1_12 (GPIO8), R31.2
TCH_B: DISP2.31 (CTP_SDA), IC1.J3_18 (GPIO21), R32.2
TCH_INT: DISP2.39 (CTP_INT), IC1.J1_15 (GPIO9)
TFT_BL: DISP2.29 (BL_ON/OFF), IC1.J1_10 (GPIO17)
TFT_CS: DISP2.23 (LCD_/CS), IC1.J1_7 (GPIO7)
TFT_DC: DISP2.25 (/WR(D/C)), IC1.J1_8 (GPIO15)
TFT_MISO: DISP2.28 (LCD_SDO), DISP2.32 (SDO), IC1.J1_6 (GPIO6)
TFT_MOSI: DISP2.27 (LCD_SDI), DISP2.34 (SDI), IC1.J1_5 (GPIO5)
TFT_RST: DISP2.21 (/RESET_NC), IC1.J1_9 (GPIO16)
TFT_SCK: DISP2.24 (D/C(SCL)), DISP2.33 (SCL), IC1.J1_4 (GPIO4)
TFT_TE: DISP2.22 (TE), IC1.J1_11 (GPIO18)

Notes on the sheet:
ESP32-S3 user interface
TFT on SPI3 via the GPIO matrix
Touch, no jumper - firmware picks the mode:
TCH_A GPIO8 resistive CS / CTP SCL
TCH_B GPIO21 PENIRQ / CTP SDA
TCH_INT GPIO9 unused / CTP INT
R31/R32 4.7k fitted in every build.
BTN_A/BTN_B: ADC1, usable with WiFi on.
TFT ER-TFTM024-3
2.4 in 240x320, 4-wire SPI, resistive touch (XPT2046)
4-wire SPI: pin 24 = SCL (clock), 25 = D/C
module: J2-J5 closed, J1/J6-J8 open
VDD 5 V (module JP open); C11/C12 at the header
/RD tied high: write-only bus
touch bus 32-34 tied to the TFT SPI (XPT2046,
own ~2 MHz clock); CS = TCH_A, PENIRQ = TCH_B
SD/FONT/FLASH CS (35-37): 10k pull-ups, so
nothing on the module drives TFT_MISO
BEFORE FIRST POWER-UP: measure MISO/TE high
level with VDD = 5 V; if it follows 5 V, run
the panel from 3V3 or add level shifting.
OLED SSD1306
0.96 in 128x64, I2C 0x3C
R26/R27 not fitted: the bus pull-ups are R6/R7
on the radio side; fit them if JP3/JP4 are cut.
Header pull-ups
touch CS/IRQ and the module flash/font/SD chip selects
Buttons
two resistor ladders on ADC1: one GPIO per ladder
DOWN
LEFT
RIGHT
BACK
SPARE (opt.)
Both ladders: 0R / 2.2k / 6.8k / 22k under a 10k pull-up -> one firmware table;
levels 0 / 0.60 / 1.34 / 2.27 / 3.3 V, thresholds 0.30 / 0.97 / 1.80 / 2.79 V. Wake: 0R keys only.

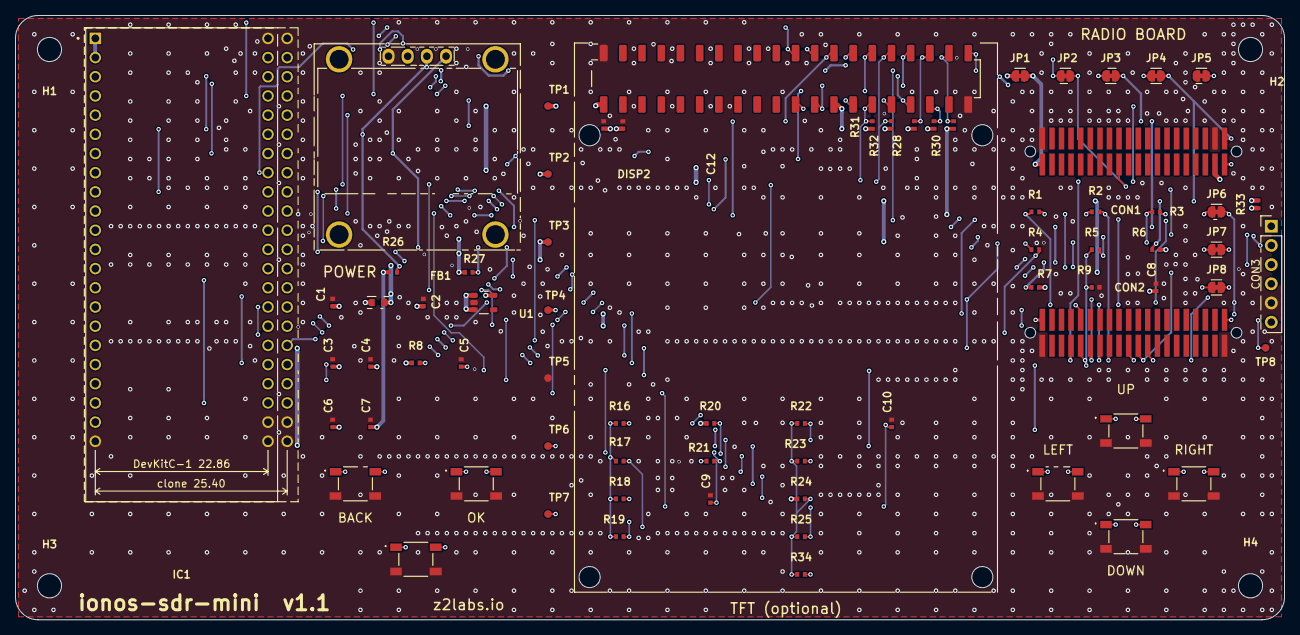
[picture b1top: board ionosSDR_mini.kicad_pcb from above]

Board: 4 copper layers, 168.0 x 80.0 mm, 78 parts (0 on the bottom side), 57 nets.
